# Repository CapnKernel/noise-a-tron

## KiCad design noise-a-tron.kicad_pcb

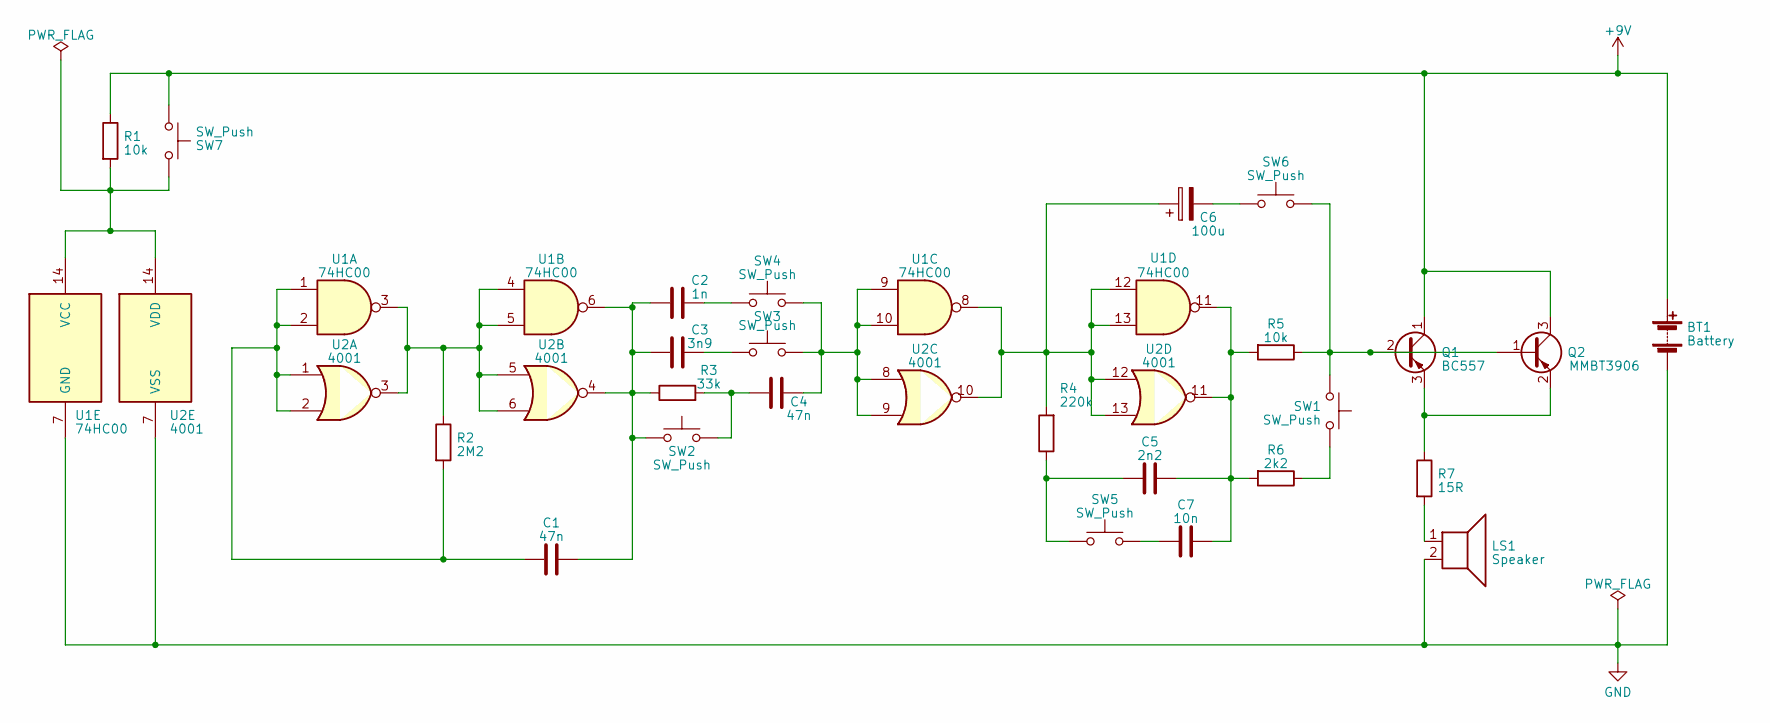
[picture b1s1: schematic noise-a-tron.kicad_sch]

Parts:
BT1: Battery; PinHeader_1x02_P2.54mm_Vertical
C1, C4: 47n; C_0805_2012Metric_Pad1.18x1.45mm_HandSolder
C2: 1n; C_0805_2012Metric_Pad1.18x1.45mm_HandSolder
C3: 3n9; C_0805_2012Metric_Pad1.18x1.45mm_HandSolder
C5: 2n2; C_0805_2012Metric_Pad1.18x1.45mm_HandSolder
C6: 100u; CP_Radial_D5.0mm_P2.00mm
C7: 10n; C_0805_2012Metric_Pad1.18x1.45mm_HandSolder
LS1: Speaker; PinHeader_1x02_P2.54mm_Vertical
Q1: BC557; TO-92_Inline
Q2: MMBT3906; SOT-23
R1, R5: 10k; R_0805_2012Metric_Pad1.20x1.40mm_HandSolder
R2: 2M2; R_0805_2012Metric_Pad1.20x1.40mm_HandSolder
R3: 33k; R_0805_2012Metric_Pad1.20x1.40mm_HandSolder
R4: 220k; R_0805_2012Metric_Pad1.20x1.40mm_HandSolder
R6: 2k2; R_0805_2012Metric_Pad1.20x1.40mm_HandSolder
R7: 15R; R_0805_2012Metric_Pad1.20x1.40mm_HandSolder
SW1, SW2, SW3, SW4, SW5, SW6, SW7: SW_Push; SW_PUSH_6mm_H5mm_and_strip
U1: 74HC00; DIP-14_W7.62mm_and_SOIC-14
U2: 4001; DIP-14_W7.62mm_and_SOIC-14

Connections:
+9V: BT1.1 (+), Q1.1 (C), Q2.3 (C), R1.1, SW7.2
GND: BT1.2 (-), LS1.2, U1.7 (GND), U2.7 (VSS)
unnamed: C1.1, C2.2, C3.2, R3.1, SW2.2, U1.6, U2.4
unnamed: C1.2, R2.2, U1.1, U1.2, U2.1, U2.2
unnamed: C2.1, SW4.2
unnamed: C3.1, SW3.2
unnamed: C4.1, SW3.1, SW4.1, U1.9, U1.10, U2.8, U2.9
unnamed: C4.2, R3.2, SW2.1
unnamed: C5.1, C7.1, R5.2, R6.2, U1.11, U2.11
unnamed: C5.2, R4.1, SW5.2
unnamed: C6.1, R4.2, U1.8, U1.12, U1.13, U2.10, U2.12, U2.13
unnamed: C6.2, SW6.1
unnamed: C7.2, SW5.1
unnamed: LS1.1, R7.2
unnamed: Q1.2 (B), Q2.1 (B), R5.1, SW1.2, SW6.2
unnamed: Q1.3 (E), Q2.2 (E), R7.1
unnamed: R2.1, U1.3, U1.4, U1.5, U2.3, U2.5, U2.6
unnamed: R6.1, SW1.1
unnamed: R1.2, SW7.1, U1.14 (VCC), U2.14 (VDD)

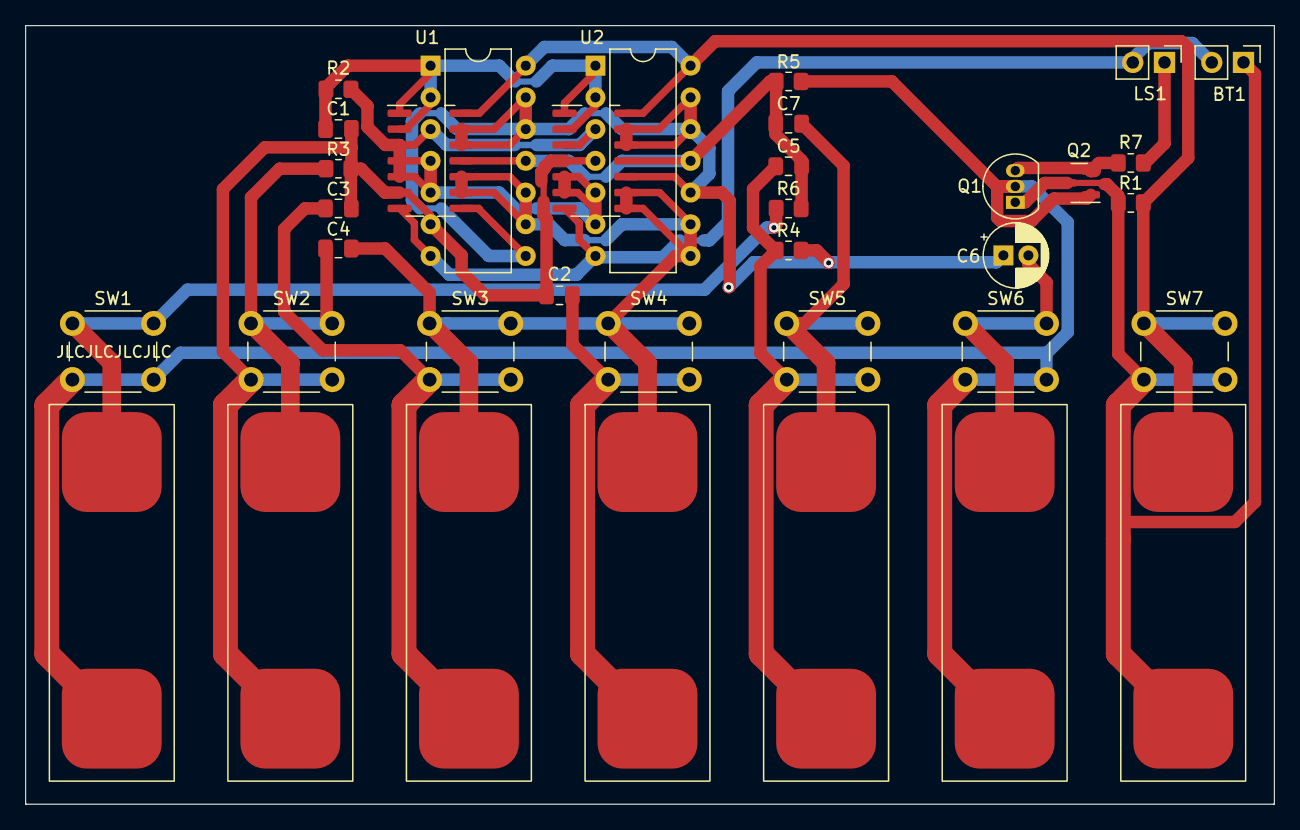
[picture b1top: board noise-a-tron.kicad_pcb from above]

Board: 2 copper layers, 100.0 x 62.3 mm, 27 parts (0 on the bottom side), 19 nets.

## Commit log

2023-05-10 v1.0a
2023-05-10 Added JLCJLCJLCJLC
